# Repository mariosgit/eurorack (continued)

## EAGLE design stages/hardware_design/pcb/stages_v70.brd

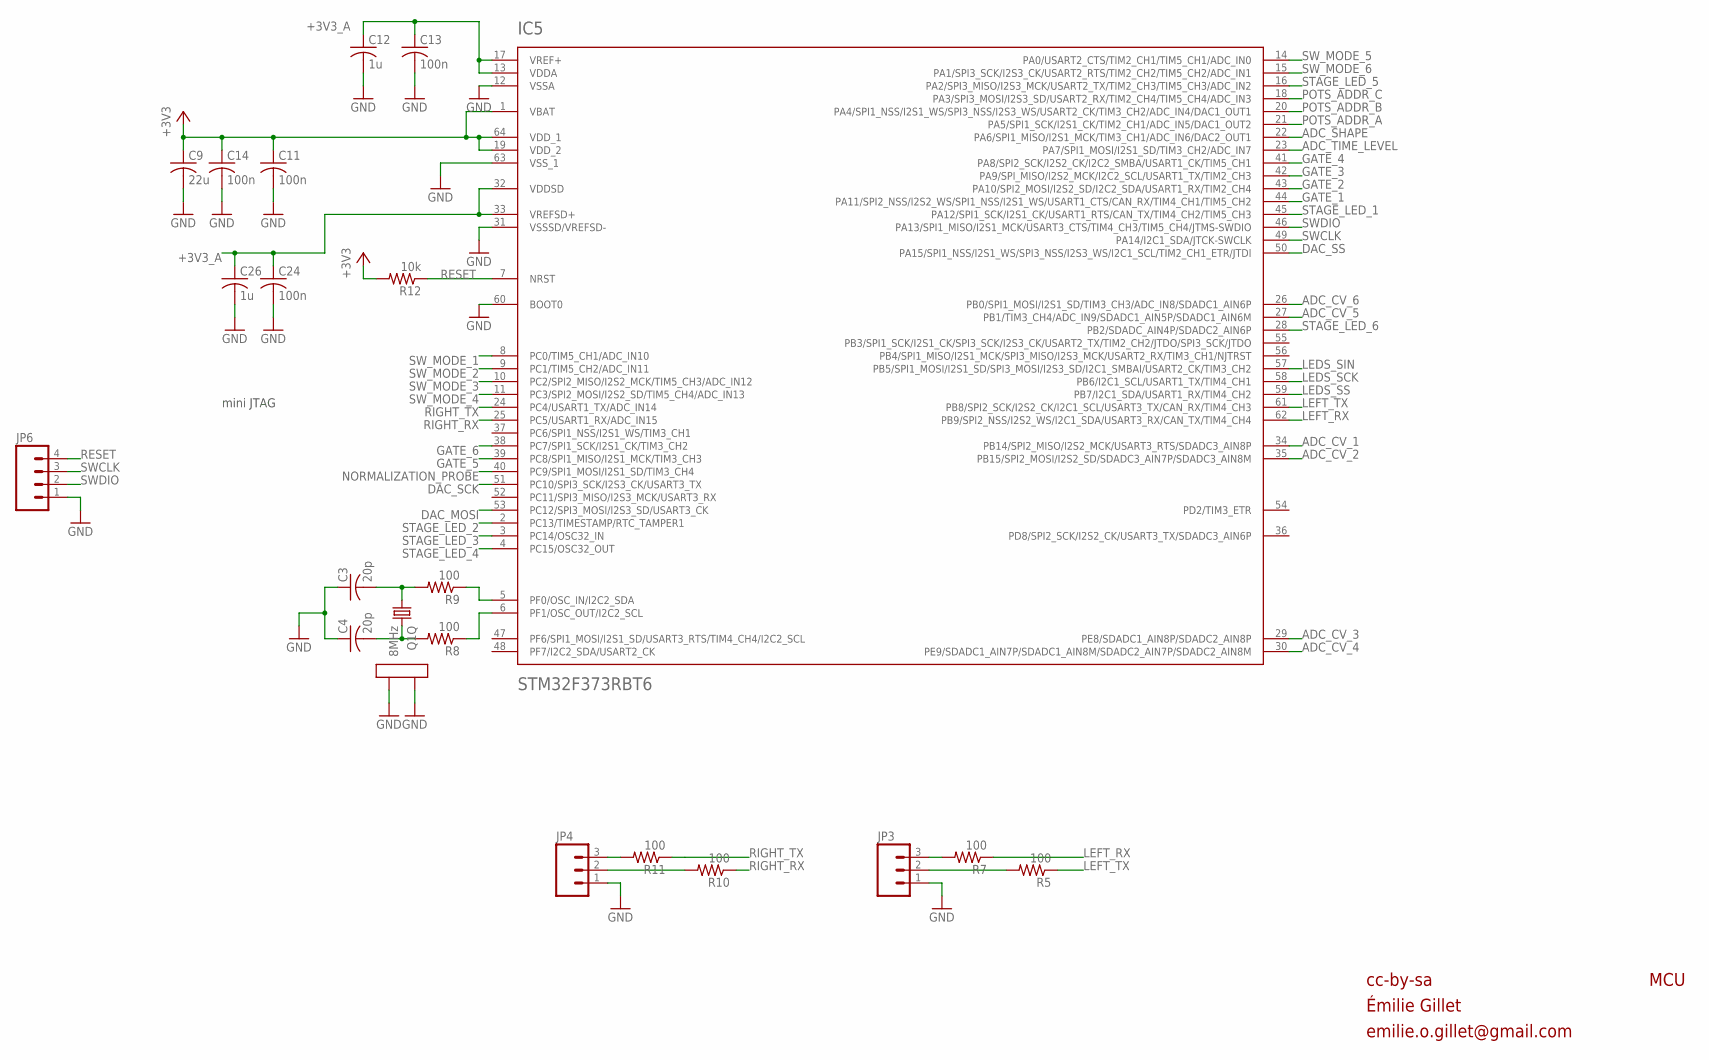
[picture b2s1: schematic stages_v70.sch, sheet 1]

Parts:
C3, C4: 20p; C0402
C9: 22u; C1206
C11, C13, C14, C24: 100n; C0402
C12, C26: 1u; C0402
IC5: STM32F373RBT6; TQFP-10X10-64
JP3, JP4: M03PTH; 1X03
JP6: M04PTH; 1X04
Q1: 8MHz; CTS406
R5, R7, R8, R9, R10, R11: 100; R0402
R12: 10k; R0402

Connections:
+3V3: C9.1, C11.1, C14.1, IC5.1 (VBAT), IC5.19 (VDD_2), IC5.64 (VDD_1), R12.2; also elsewhere on the board
+3V3_A: C12.1, C13.1, C24.1, C26.1, IC5.13 (VDDA), IC5.17 (VREF+), IC5.32 (VDDSD), IC5.33 (VREFSD+); also elsewhere on the board
ADC_CV_1: IC5.34 (PB14/SPI2_MISO/I2S2_MCK/USART3_RTS/SDAD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); also elsewhere on the board
ADC_CV_2: IC5.35 (PB15/SPI2_MOSI/I2S2_SD/SDADC3_AIN7P/SDA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); also elsewhere on the board
ADC_CV_3: IC5.29 (PE8/SDADC1_AIN8P/SDADC2_AIN8P); also elsewhere on the board
ADC_CV_4: IC5.30 (PE9/SDADC1_AIN7P/SDADC1_AIN8M/SDADC2_AI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); also elsewhere on the board
ADC_CV_5: IC5.27 (PB1/TIM3_CH4/ADC_IN9/SDADC1_AIN5P/SDADC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); also elsewhere on the board
ADC_CV_6: IC5.26 (PB0/SPI1_MOSI/I2S1_SD/TIM3_CH3/ADC_IN8/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); also elsewhere on the board
ADC_SHAPE: IC5.22 (PA6/SPI1_MISO/I2S1_MCK/TIM3_CH1/ADC_IN6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); also elsewhere on the board
ADC_TIME_LEVEL: IC5.23 (PA7/SPI1_MOSI/I2S1_SD/TIM3_CH2/ADC_IN7); also elsewhere on the board
DAC_MOSI: IC5.53 (PC12/SPI3_MOSI/I2S3_SD/USART3_CK); also elsewhere on the board
DAC_SCK: IC5.51 (PC10/SPI3_SCK/I2S3_CK/USART3_TX); also elsewhere on the board
DAC_SS: IC5.50 (PA15/SPI1_NSS/I2S1_WS/SPI3_NSS/I2S3_WS/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); also elsewhere on the board
GATE_1: IC5.44 (PA11/SPI2_NSS/I2S2_WS/SPI1_NSS/I2S1_WS/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); also elsewhere on the board
GATE_2: IC5.43 (PA10/SPI2_MOSI/I2S2_SD/I2C2_SDA/USART1_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); also elsewhere on the board
GATE_3: IC5.42 (PA9/SPI_MISO/I2S2_MCK/I2C2_SCL/USART1_T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); also elsewhere on the board
GATE_4: IC5.41 (PA8/SPI2_SCK/I2S2_CK/I2C2_SMBA/USART1_C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); also elsewhere on the board
GATE_5: IC5.39 (PC8/SPI1_MISO/I2S1_MCK/TIM3_CH3); also elsewhere on the board
GATE_6: IC5.38 (PC7/SPI1_SCK/I2S1_CK/TIM3_CH2); also elsewhere on the board
GND: C3.1, C4.1, C9.2, C11.2, C12.2, C13.2, C14.2, C24.2, C26.2, IC5.12 (VSSA), IC5.31 (VSSSD/VREFSD-), IC5.60 (BOOT0), IC5.63 (VSS_1), JP3.1, JP4.1, JP6.1, Q1.2 (LID1), Q1.4 (LID2); also elsewhere on the board
LEDS_SCK: IC5.58 (PB6/I2C1_SCL/USART1_TX/TIM4_CH1); also elsewhere on the board
LEDS_SIN: IC5.57 (PB5/SPI1_MOSI/I2S1_SD/SPI3_MOSI/I2S3_SD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); also elsewhere on the board
LEDS_SS: IC5.59 (PB7/I2C1_SDA/USART1_RX/TIM4_CH2); also elsewhere on the board
LEFT_RX: IC5.62 (PB9/SPI2_NSS/I2S2_WS/I2C1_SDA/USART3_RX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), R7.1
LEFT_RX_R: JP3.3, R7.2
LEFT_TX: IC5.61 (PB8/SPI2_SCK/I2S2_CK/I2C1_SCL/USART3_TX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), R5.1
LEFT_TX_R: JP3.2, R5.2
unnamed: C3.2, Q1.1, R9.2
unnamed: C4.2, Q1.3 (2), R8.2
unnamed: IC5.5 (PF0/OSC_IN/I2C2_SDA), R9.1
unnamed: IC5.6 (PF1/OSC_OUT/I2C2_SCL), R8.1
NORMALIZATION_PROBE: IC5.40 (PC9/SPI1_MOSI/I2S1_SD/TIM3_CH4); also elsewhere on the board
POTS_ADDR_A: IC5.21 (PA5/SPI1_SCK/I2S1_CK/TIM2_CH1/ADC_IN5/D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); also elsewhere on the board
POTS_ADDR_B: IC5.20 (PA4/SPI1_NSS/I2S1_WS/SPI3_NSS/I2S3_WS/U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); also elsewhere on the board
POTS_ADDR_C: IC5.18 (PA3/SPI3_MOSI/I2S3_SD/USART2_RX/TIM2_CH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); also elsewhere on the board
RESET: IC5.7 (NRST), JP6.4, R12.1
RIGHT_RX: IC5.25 (PC5/USART1_RX/ADC_IN15), R10.1
RIGHT_RX_R: JP4.2, R10.2
RIGHT_TX: IC5.24 (PC4/USART1_TX/ADC_IN14), R11.1
RIGHT_TX_R: JP4.3, R11.2
STAGE_LED_1: IC5.45 (PA12/SPI1_SCK/I2S1_CK/USART1_RTS/CAN_TX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); also elsewhere on the board
STAGE_LED_2: IC5.2 (PC13/TIMESTAMP/RTC_TAMPER1); also elsewhere on the board
STAGE_LED_3: IC5.3 (PC14/OSC32_IN); also elsewhere on the board
STAGE_LED_4: IC5.4 (PC15/OSC32_OUT); also elsewhere on the board
STAGE_LED_5: IC5.16 (PA2/SPI3_MISO/I2S3_MCK/USART2_TX/TIM2_C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); also elsewhere on the board
STAGE_LED_6: IC5.28 (PB2/SDADC_AIN4P/SDADC2_AIN6P); also elsewhere on the board
SWCLK: IC5.49 (PA14/I2C1_SDA/JTCK-SWCLK), JP6.3
SWDIO: IC5.46 (PA13/SPI1_MISO/I2S1_MCK/USART3_CTS/TIM4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), JP6.2
SW_MODE_1: IC5.8 (PC0/TIM5_CH1/ADC_IN10); also elsewhere on the board
SW_MODE_2: IC5.9 (PC1/TIM5_CH2/ADC_IN11); also elsewhere on the board
SW_MODE_3: IC5.10 (PC2/SPI2_MISO/I2S2_MCK/TIM5_CH3/ADC_IN12); also elsewhere on the board
SW_MODE_4: IC5.11 (PC3/SPI2_MOSI/I2S2_SD/TIM5_CH4/ADC_IN13); also elsewhere on the board
SW_MODE_5: IC5.14 (PA0/USART2_CTS/TIM2_CH1/TIM5_CH1/ADC_IN0); also elsewhere on the board
SW_MODE_6: IC5.15 (PA1/SPI3_SCK/I2S3_CK/USART2_RTS/TIM2_CH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); also elsewhere on the board

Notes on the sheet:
cc-by-sa
MCU
mini JTAG
Émilie Gillet
emilie.o.gillet@gmail.com

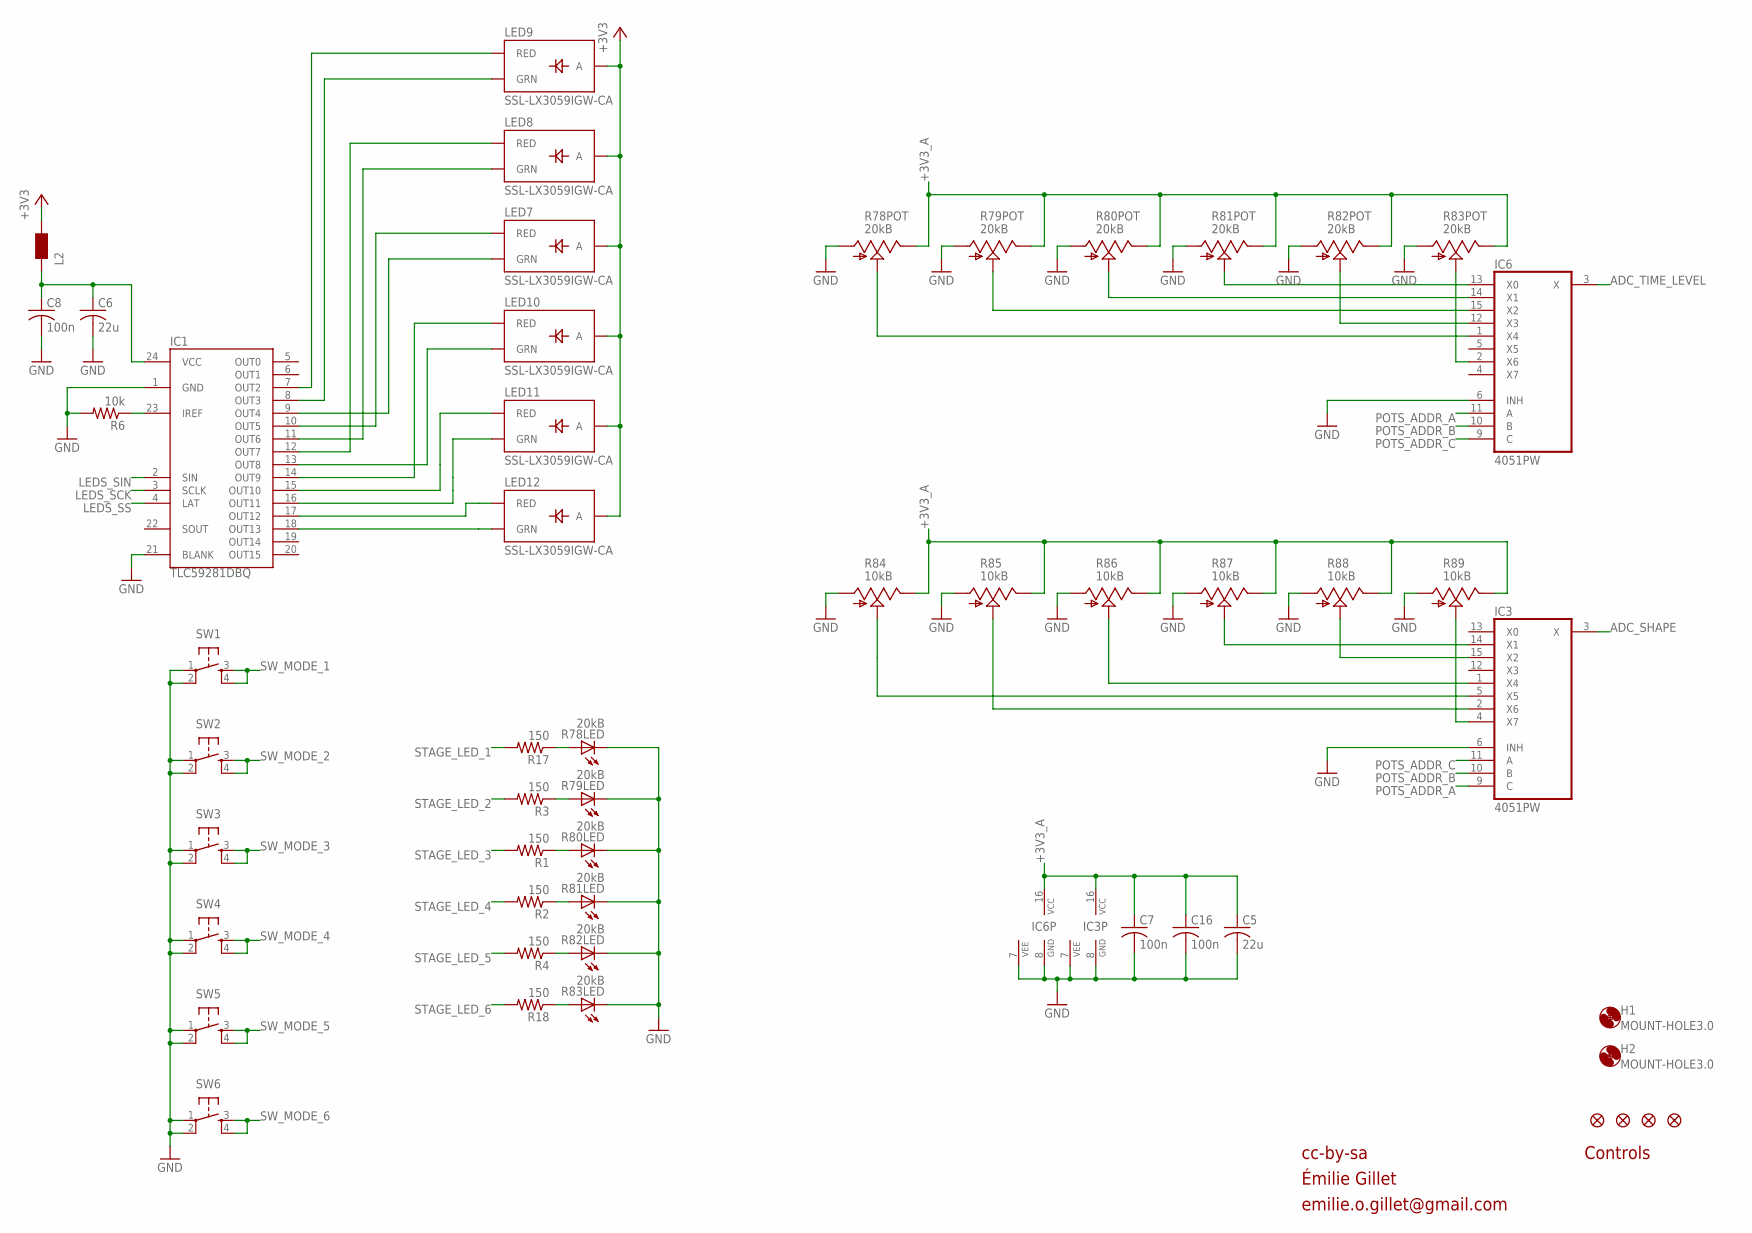
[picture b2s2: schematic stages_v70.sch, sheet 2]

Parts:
C5, C6: 22u; C1206
C7, C8, C16: 100n; C0402
H1, H2: MOUNT-HOLE3.0; 3,0
IC1: TLC59281DBQ; TSSOP24_0635
IC3, IC6: 4051PW; TSSOP16_065
JP1, JP2, JP7, JP8: FIDUCIAL1X2; FIDUCIAL-1X2
L2: WE-CBF_0603; 0603
LED7, LED8, LED9, LED10, LED11, LED12: SSL-LX3059IGW-CA; LED-BICOLOR-THROUGHHOLE-LUMEX
R1, R2, R3, R4, R17, R18: 150; R0402
R6: 10k; R0402
R78, R79, R80, R81, R82, R83: 20kB; BOURNS_SLIDER
R84, R85, R86, R87, R88, R89: 10kB; ALPS_POT_NARROW
SW1, SW2, SW3, SW4, SW5, SW6: TAC_SWITCHPTH; TACTILE-PTH

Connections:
+3V3: L2.2, LED7.A, LED8.A, LED9.A, LED10.A, LED11.A, LED12.A; also elsewhere on the board
+3V3_A: C5.1, C7.1, C16.1, IC3.16 (VCC), IC6.16 (VCC), R78.3 (E), R79.3 (E), R80.3 (E), R81.3 (E), R82.3 (E), R83.3 (E), R84.P$1 (E), R85.P$1 (E), R86.P$1 (E), R87.P$1 (E), R88.P$1 (E), R89.P$1 (E); also elsewhere on the board
ADC_SHAPE: IC3.3 (X); also elsewhere on the board
ADC_TIME_LEVEL: IC6.3 (X); also elsewhere on the board
GND: C5.2, C6.2, C7.2, C8.2, C16.2, IC1.1 (GND), IC1.21 (BLANK), IC3.6 (INH), IC3.7 (VEE), IC3.8 (GND), IC6.6 (INH), IC6.7 (VEE), IC6.8 (GND), R6.2, R78.1 (A), R78.E (C), R79.1 (A), R79.E (C), R80.1 (A), R80.E (C), R81.1 (A), R81.E (C), R82.1 (A), R82.E (C), R83.1 (A), R83.E (C), R84.P$3 (A), R85.P$3 (A), R86.P$3 (A), R87.P$3 (A), R88.P$3 (A), R89.P$3 (A), SW1.1, SW1.2, SW2.1, SW2.2, SW3.1, SW3.2, SW4.1, SW4.2, SW5.1, SW5.2, SW6.1, SW6.2; also elsewhere on the board
LEDS_SCK: IC1.3 (SCLK); also elsewhere on the board
LEDS_SIN: IC1.2 (SIN); also elsewhere on the board
LEDS_SS: IC1.4 (LAT); also elsewhere on the board
unnamed: IC1.10 (OUT5), LED7.RED_C (RED)
unnamed: IC1.18 (OUT13), LED12.GREEN_C (GRN)
unnamed: IC1.12 (OUT7), LED8.RED_C (RED)
unnamed: IC1.7 (OUT2), LED9.RED_C (RED)
unnamed: IC1.8 (OUT3), LED9.GREEN_C (GRN)
unnamed: IC1.13 (OUT8), LED10.GREEN_C (GRN)
unnamed: IC1.15 (OUT10), LED11.RED_C (RED)
unnamed: R17.1, R78.B (A)
unnamed: IC1.16 (OUT11), LED11.GREEN_C (GRN)
unnamed: IC1.17 (OUT12), LED12.RED_C (RED)
unnamed: IC1.11 (OUT6), LED8.GREEN_C (GRN)
unnamed: C6.1, C8.1, IC1.24 (VCC), L2.1
unnamed: IC1.14 (OUT9), LED10.RED_C (RED)
unnamed: IC6.1 (X4), R78.2 (S)
unnamed: R18.1, R83.B (A)
unnamed: IC6.2 (X6), R83.2 (S)
unnamed: IC6.12 (X3), R82.2 (S)
unnamed: IC6.13 (X0), R81.2 (S)
unnamed: IC6.14 (X1), R80.2 (S)
unnamed: IC6.15 (X2), R79.2 (S)
unnamed: IC3.2 (X6), R85.P$2 (S)
unnamed: IC3.4 (X7), R89.P$2 (S)
unnamed: IC3.1 (X4), R86.P$2 (S)
unnamed: IC3.14 (X1), R87.P$2 (S)
unnamed: IC3.15 (X2), R88.P$2 (S)
unnamed: IC3.5 (X5), R84.P$2 (S)
unnamed: R4.1, R82.B (A)
unnamed: IC1.23 (IREF), R6.1
unnamed: R2.1, R81.B (A)
unnamed: IC1.9 (OUT4), LED7.GREEN_C (GRN)
unnamed: R1.1, R80.B (A)
unnamed: R3.1, R79.B (A)
POTS_ADDR_A: IC3.9 (C), IC6.11 (A); also elsewhere on the board
POTS_ADDR_B: IC3.10 (B), IC6.10 (B); also elsewhere on the board
POTS_ADDR_C: IC3.11 (A), IC6.9 (C); also elsewhere on the board
STAGE_LED_1: R17.2; also elsewhere on the board
STAGE_LED_2: R3.2; also elsewhere on the board
STAGE_LED_3: R1.2; also elsewhere on the board
STAGE_LED_4: R2.2; also elsewhere on the board
STAGE_LED_5: R4.2; also elsewhere on the board
STAGE_LED_6: R18.2; also elsewhere on the board
SW_MODE_1: SW1.3, SW1.4; also elsewhere on the board
SW_MODE_2: SW2.3, SW2.4; also elsewhere on the board
SW_MODE_3: SW3.3, SW3.4; also elsewhere on the board
SW_MODE_4: SW4.3, SW4.4; also elsewhere on the board
SW_MODE_5: SW5.3, SW5.4; also elsewhere on the board
SW_MODE_6: SW6.3, SW6.4; also elsewhere on the board

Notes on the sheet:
cc-by-sa
Controls
Émilie Gillet
emilie.o.gillet@gmail.com

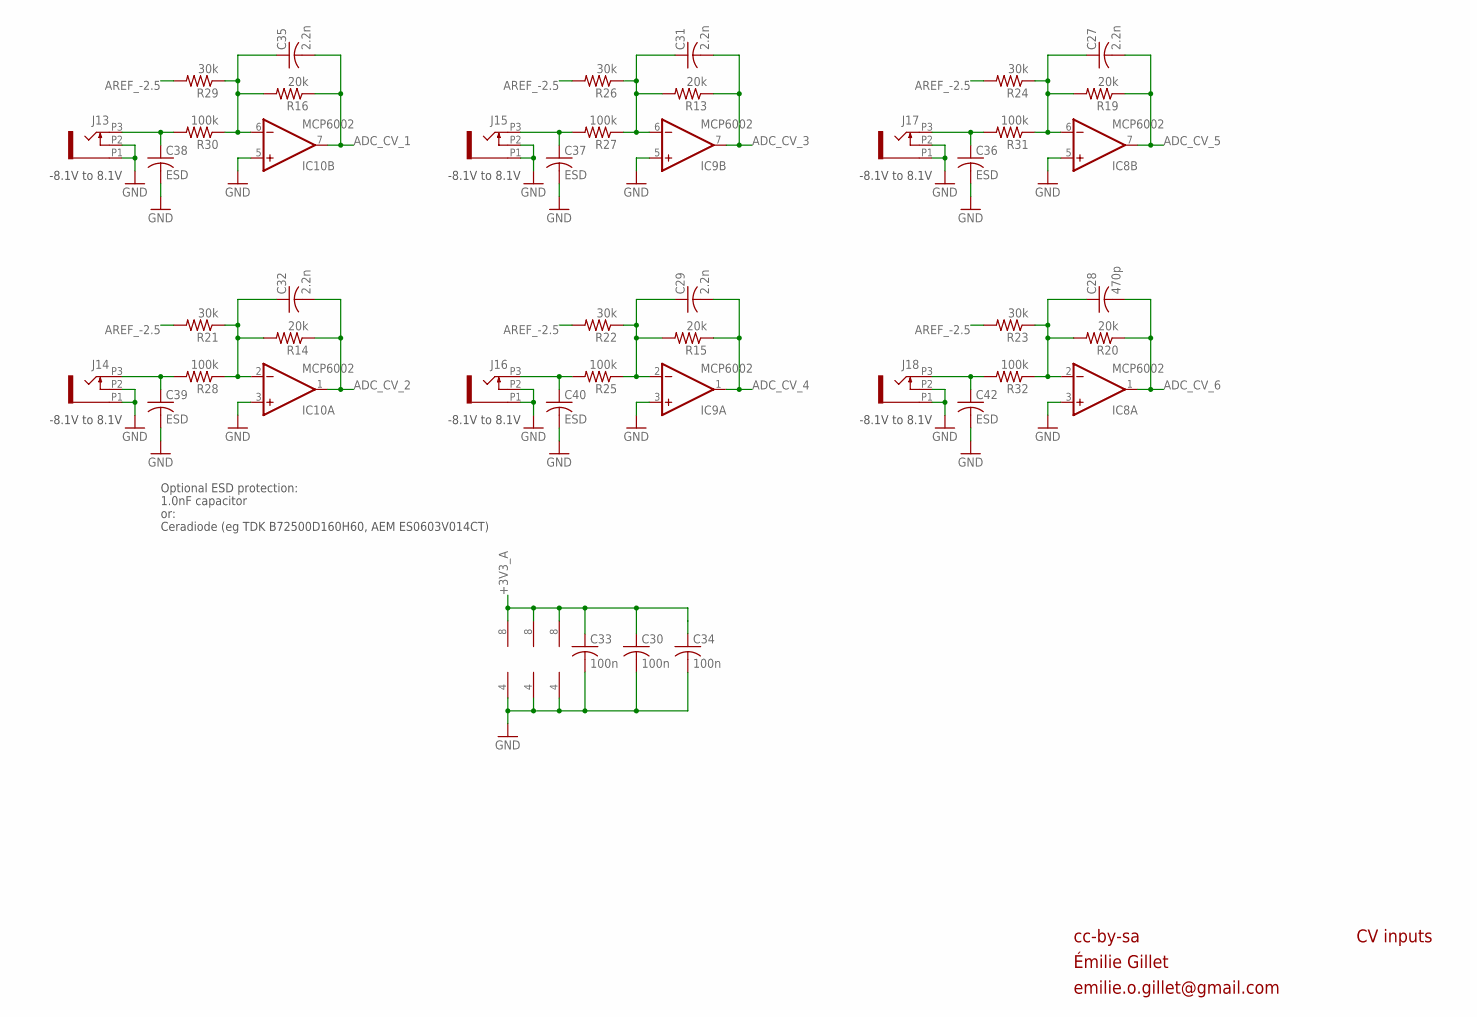
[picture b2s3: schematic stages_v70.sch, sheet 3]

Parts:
C27, C29, C31, C32, C35: 2.2n; C0402
C28: 470p; C0402
C30, C33, C34: 100n; C0402
C36, C37, C38, C39, C40, C42: ESD; C0603
IC8, IC9, IC10: MCP6002; MSOP-8
J13, J14, J15, J16, J17, J18: PJ301_THONKICONN6; WQP_PJ_301M6
R13, R14, R15, R16, R19, R20: 20k; R0402
R21, R22, R23, R24, R26, R29: 30k; R0402
R25, R27, R28, R30, R31, R32: 100k; R0402

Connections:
+3V3_A: C30.1, C33.1, C34.1, IC8.8 (V+), IC9.8 (V+), IC10.8 (V+); also elsewhere on the board
ADC_CV_1: C35.2, IC10.7 (OUT), R16.1; also elsewhere on the board
ADC_CV_2: C32.2, IC10.1 (OUT), R14.1; also elsewhere on the board
ADC_CV_3: C31.2, IC9.7 (OUT), R13.1; also elsewhere on the board
ADC_CV_4: C29.2, IC9.1 (OUT), R15.1; also elsewhere on the board
ADC_CV_5: C27.2, IC8.7 (OUT), R19.1; also elsewhere on the board
ADC_CV_6: C28.2, IC8.1 (OUT), R20.1; also elsewhere on the board
AREF_-2.5: R21.2, R22.2, R23.2, R24.2, R26.2, R29.2; also elsewhere on the board
GND: C30.2, C33.2, C34.2, C36.2, C37.2, C38.2, C39.2, C40.2, C42.2, IC8.3 (+IN), IC8.4 (V-), IC8.5 (+IN), IC9.3 (+IN), IC9.4 (V-), IC9.5 (+IN), IC10.3 (+IN), IC10.4 (V-), IC10.5 (+IN), J13.P1 (1), J13.P2 (2), J14.P1 (1), J14.P2 (2), J15.P1 (1), J15.P2 (2), J16.P1 (1), J16.P2 (2), J17.P1 (1), J17.P2 (2), J18.P1 (1), J18.P2 (2); also elsewhere on the board
MORPH_IN: C38.1, J13.P3 (3), R30.2
MORPH_IN1: C39.1, J14.P3 (3), R28.2
MORPH_IN2: C37.1, J15.P3 (3), R27.2
MORPH_IN3: C40.1, J16.P3 (3), R25.2
MORPH_IN4: C36.1, J17.P3 (3), R31.2
MORPH_IN5: C42.1, J18.P3 (3), R32.2
unnamed: C35.1, IC10.6 (-IN), R16.2, R29.1, R30.1
unnamed: C32.1, IC10.2 (-IN), R14.2, R21.1, R28.1
unnamed: C31.1, IC9.6 (-IN), R13.2, R26.1, R27.1
unnamed: C29.1, IC9.2 (-IN), R15.2, R22.1, R25.1
unnamed: C27.1, IC8.6 (-IN), R19.2, R24.1, R31.1
unnamed: C28.1, IC8.2 (-IN), R20.2, R23.1, R32.1

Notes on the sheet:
cc-by-sa
CV inputs
-8.1V to 8.1V
Optional ESD protection:
1.0nF capacitor
or:
Ceradiode (eg TDK B72500D160H60, AEM ES0603V014CT)
Émilie Gillet
emilie.o.gillet@gmail.com

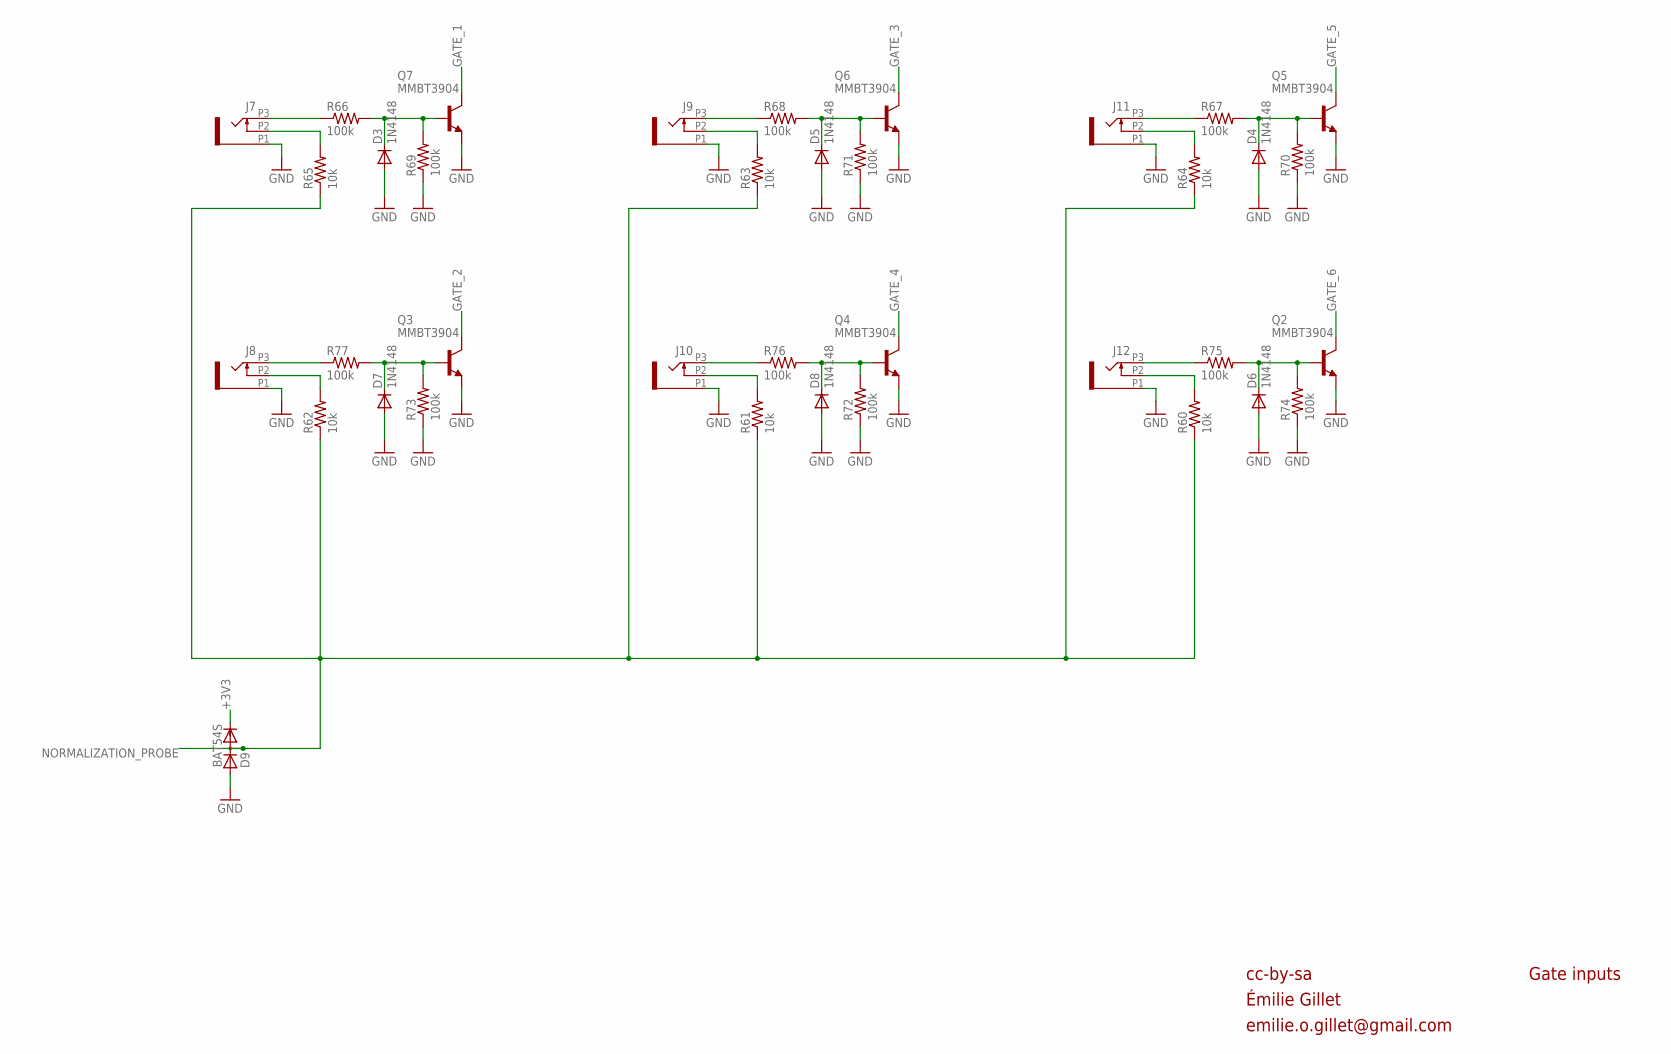
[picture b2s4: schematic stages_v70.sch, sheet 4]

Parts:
D3, D4, D5, D6, D7, D8: 1N4148; SOD523
D9: BAT54S; SOT23
J7, J8, J9, J10, J11, J12: PJ301_THONKICONN6; WQP_PJ_301M6
Q2, Q3, Q4, Q5, Q6, Q7: MMBT3904; SOT23-BEC
R60, R61, R62, R63, R64, R65: 10k; R0402
R66, R67, R68, R69, R70, R71, R72, R73, R74, R75, R76, R77: 100k; R0402

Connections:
+3V3: D9.2 (C); also elsewhere on the board
GATE_1: Q7.C; also elsewhere on the board
GATE_2: Q3.C; also elsewhere on the board
GATE_3: Q6.C; also elsewhere on the board
GATE_4: Q4.C; also elsewhere on the board
GATE_5: Q5.C; also elsewhere on the board
GATE_6: Q2.C; also elsewhere on the board
GND: D3.A, D4.A, D5.A, D6.A, D7.A, D8.A, D9.1 (A), J7.P1 (1), J8.P1 (1), J9.P1 (1), J10.P1 (1), J11.P1 (1), J12.P1 (1), Q2.E, Q3.E, Q4.E, Q5.E, Q6.E, Q7.E, R69.1, R70.1, R71.1, R72.1, R73.1, R74.1; also elsewhere on the board
unnamed: J9.P3 (3), R68.1
unnamed: J10.P3 (3), R76.1
unnamed: J10.P2 (2), R61.2
unnamed: J9.P2 (2), R63.2
unnamed: D5.C, Q6.B, R68.2, R71.2
unnamed: D8.C, Q4.B, R72.2, R76.2
unnamed: J11.P3 (3), R67.1
unnamed: J12.P3 (3), R75.1
unnamed: J12.P2 (2), R60.2
unnamed: J11.P2 (2), R64.2
unnamed: D4.C, Q5.B, R67.2, R70.2
unnamed: D6.C, Q2.B, R74.2, R75.2
unnamed: J8.P3 (3), R77.1
unnamed: J8.P2 (2), R62.2
unnamed: J7.P2 (2), R65.2
unnamed: D3.C, Q7.B, R66.2, R69.2
unnamed: D7.C, Q3.B, R73.2, R77.2
unnamed: J7.P3 (3), R66.1
NORMALIZATION_PROBE: D9.3 (AC), R60.1, R61.1, R62.1, R63.1, R64.1, R65.1; also elsewhere on the board

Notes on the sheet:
cc-by-sa
Gate inputs
Émilie Gillet
emilie.o.gillet@gmail.com

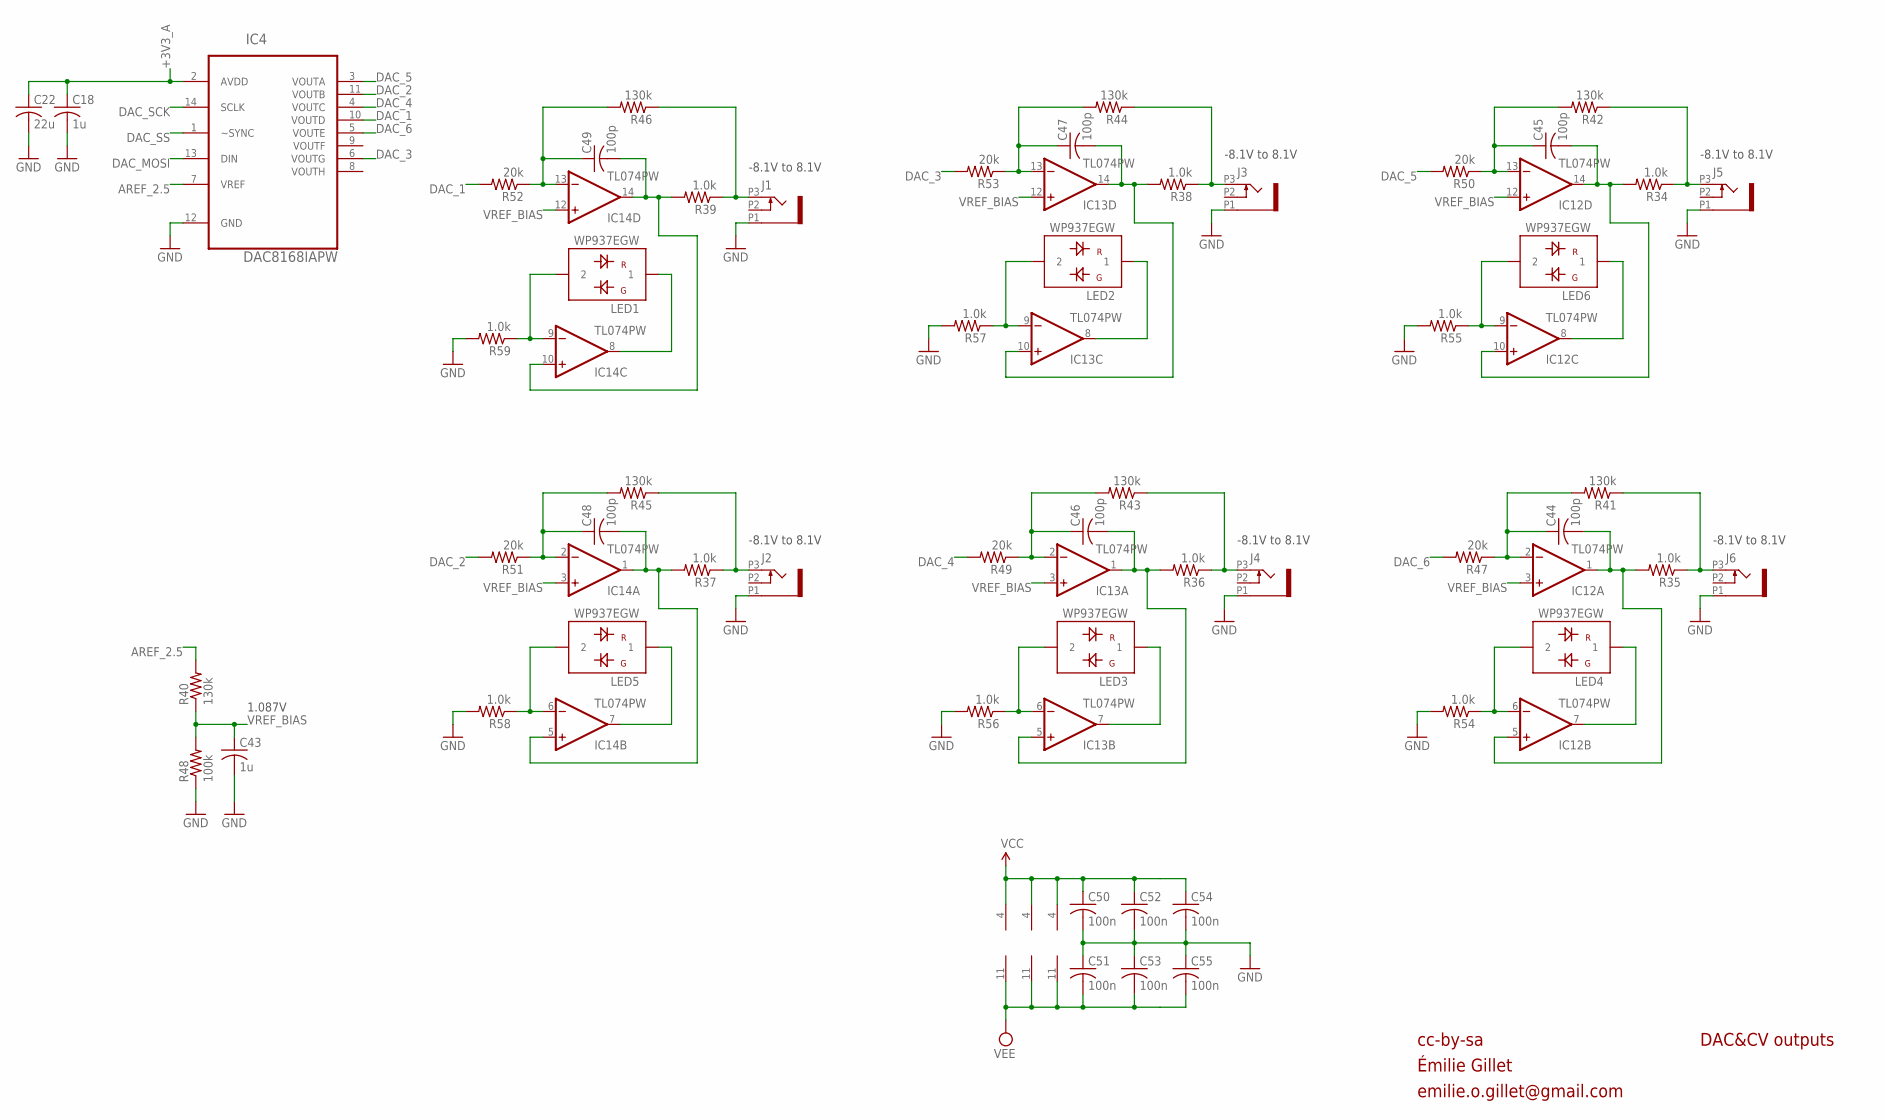
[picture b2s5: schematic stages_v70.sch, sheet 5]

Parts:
C18, C43: 1u; C0402
C22: 22u; C1206
C44, C45, C46, C47, C48, C49: 100p; C0402
C50, C51, C52, C53, C54, C55: 100n; C0402
IC4: DAC8168IAPW; RPDSOG14
IC12, IC13, IC14: TL074PW; TSSOP14_065
J1, J2, J3, J4, J5, J6: PJ301_THONKICONN6; WQP_PJ_301M6
LED1, LED2, LED3, LED4, LED5, LED6: WP937EGW; LED3MM
R34, R35, R36, R37, R38, R39: 1.0k; R0603
R40, R41, R42, R43, R44, R45, R46: 130k; R0402
R47, R49, R50, R51, R52, R53: 20k; R0402
R48: 100k; R0402
R54, R55, R56, R57, R58, R59: 1.0k; R0402

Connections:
+3V3_A: C18.1, C22.1, IC4.2 (AVDD); also elsewhere on the board
AREF_2.5: IC4.7 (VREF), R40.2
DAC_1: IC4.10 (VOUTD), R52.2
DAC_2: IC4.11 (VOUTB), R51.2
DAC_3: IC4.6 (VOUTG), R53.2
DAC_4: IC4.4 (VOUTC), R49.2
DAC_5: IC4.3 (VOUTA), R50.2
DAC_6: IC4.5 (VOUTE), R47.2
DAC_MOSI: IC4.13 (DIN); also elsewhere on the board
DAC_SCK: IC4.14 (SCLK); also elsewhere on the board
DAC_SS: IC4.1 (~SYNC); also elsewhere on the board
GND: C18.2, C22.2, C43.2, C50.2, C51.1, C52.2, C53.1, C54.2, C55.1, IC4.12 (GND), J1.P1 (1), J2.P1 (1), J3.P1 (1), J4.P1 (1), J5.P1 (1), J6.P1 (1), R48.1, R54.2, R55.2, R56.2, R57.2, R58.2, R59.2; also elsewhere on the board
unnamed: C49.2, IC14.10 (+IN), IC14.14 (OUT), R39.2
unnamed: J1.P3 (3), R39.1, R46.1
unnamed: J2.P3 (3), R37.1, R45.1
unnamed: J4.P3 (3), R36.1, R43.1
unnamed: C46.1, IC13.2 (-IN), R43.2, R49.1
unnamed: C48.1, IC14.2 (-IN), R45.2, R51.1
unnamed: C47.1, IC13.13 (-IN), R44.2, R53.1
unnamed: C49.1, IC14.13 (-IN), R46.2, R52.1
unnamed: J3.P3 (3), R38.1, R44.1
unnamed: IC14.9 (-IN), LED1.2, R59.1
unnamed: IC14.8 (OUT), LED1.1
unnamed: C47.2, IC13.10 (+IN), IC13.14 (OUT), R38.2
unnamed: IC13.9 (-IN), LED2.2, R57.1
unnamed: IC13.8 (OUT), LED2.1
unnamed: C48.2, IC14.1 (OUT), IC14.5 (+IN), R37.2
unnamed: IC14.6 (-IN), LED5.2, R58.1
unnamed: IC14.7 (OUT), LED5.1
unnamed: C46.2, IC13.1 (OUT), IC13.5 (+IN), R36.2
unnamed: IC13.6 (-IN), LED3.2, R56.1
unnamed: IC13.7 (OUT), LED3.1
unnamed: J6.P3 (3), R35.1, R41.1
unnamed: C44.1, IC12.2 (-IN), R41.2, R47.1
unnamed: C45.1, IC12.13 (-IN), R42.2, R50.1
unnamed: J5.P3 (3), R34.1, R42.1
unnamed: C45.2, IC12.10 (+IN), IC12.14 (OUT), R34.2
unnamed: IC12.9 (-IN), LED6.2, R55.1
unnamed: IC12.8 (OUT), LED6.1
unnamed: C44.2, IC12.1 (OUT), IC12.5 (+IN), R35.2
unnamed: IC12.6 (-IN), LED4.2, R54.1
unnamed: IC12.7 (OUT), LED4.1
VCC: C50.1, C52.1, C54.1, IC12.4 (V+), IC13.4 (V+), IC14.4 (V+); also elsewhere on the board
VEE: C51.2, C53.2, C55.2, IC12.11 (V-), IC13.11 (V-), IC14.11 (V-); also elsewhere on the board
VREF_BIAS: C43.1, IC12.3 (+IN), IC12.12 (+IN), IC13.3 (+IN), IC13.12 (+IN), IC14.3 (+IN), IC14.12 (+IN), R40.1, R48.2

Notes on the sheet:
cc-by-sa
DAC&CV outputs
-8.1V to 8.1V
1.087V
Émilie Gillet
emilie.o.gillet@gmail.com

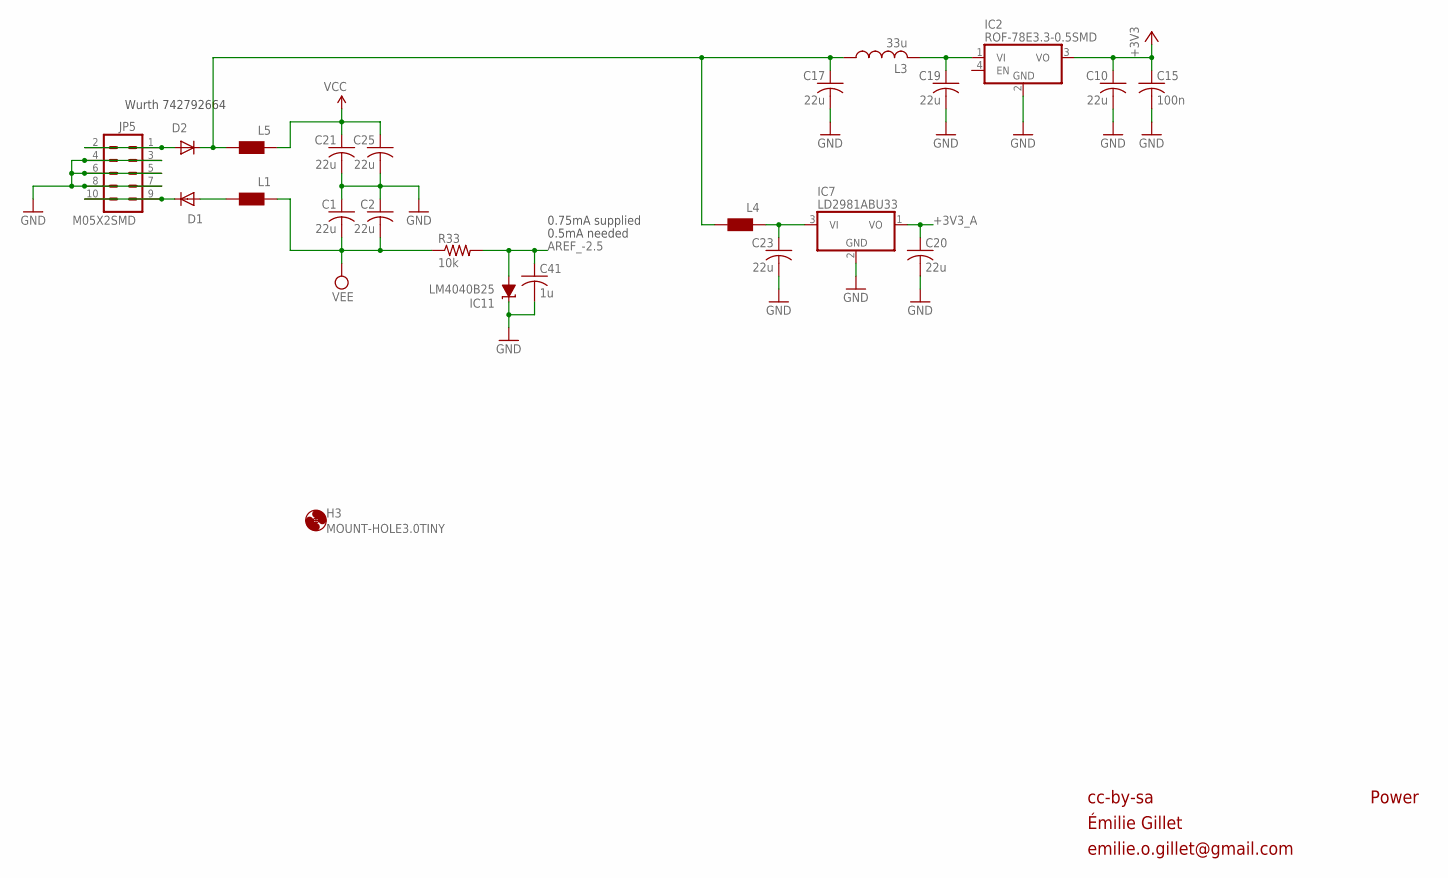
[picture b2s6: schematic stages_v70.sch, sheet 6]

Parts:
C1, C2, C10, C17, C19, C20, C21, C23, C25: 22u; C1206
C15: 100n; C0402
C41: 1u; C0402
D1, D2: 1N5819HW; SOD123
H3: MOUNT-HOLE3.0TINY; 3,0TINY
IC2: ROF-78E3.3-0.5SMD; ROF78EXX-0.5SMD
IC7: LD2981ABU33; SOT89
IC11: LM4040B25; DBZ_R-PDSO-G3
JP5: M05X2SMD; 2X5-SMD
L1, L4, L5: WE-CBF_0603; 0603
L3: 33u; L2012C
R33: 10k; R0402

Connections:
+3V3: C10.1, C15.1, IC2.3 (VO); also elsewhere on the board
+3V3_A: C20.1, IC7.1 (VO); also elsewhere on the board
AREF_-2.5: C41.1, IC11.2 (A), R33.2; also elsewhere on the board
GND: C1.1, C2.1, C10.2, C15.2, C17.2, C19.2, C20.2, C21.2, C23.2, C25.2, C41.2, IC2.2 (GND), IC7.2 (GND), IC11.1 (C), JP5.3, JP5.4, JP5.5, JP5.6, JP5.7, JP5.8; also elsewhere on the board
unnamed: D2.A, JP5.1, JP5.2
unnamed: D1.A, L1.2
unnamed: C23.1, IC7.3 (VI), L4.1
unnamed: C17.1, D2.C, L3.1, L4.2, L5.2
unnamed: D1.C, JP5.9, JP5.10
unnamed: C19.1, IC2.1 (VI), L3.2
VCC: C21.1, C25.1, L5.1; also elsewhere on the board
VEE: C1.2, C2.2, L1.1, R33.1; also elsewhere on the board

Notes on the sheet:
0.5mA needed
Wurth 742792664
0.75mA supplied
cc-by-sa
Power
Émilie Gillet
emilie.o.gillet@gmail.com

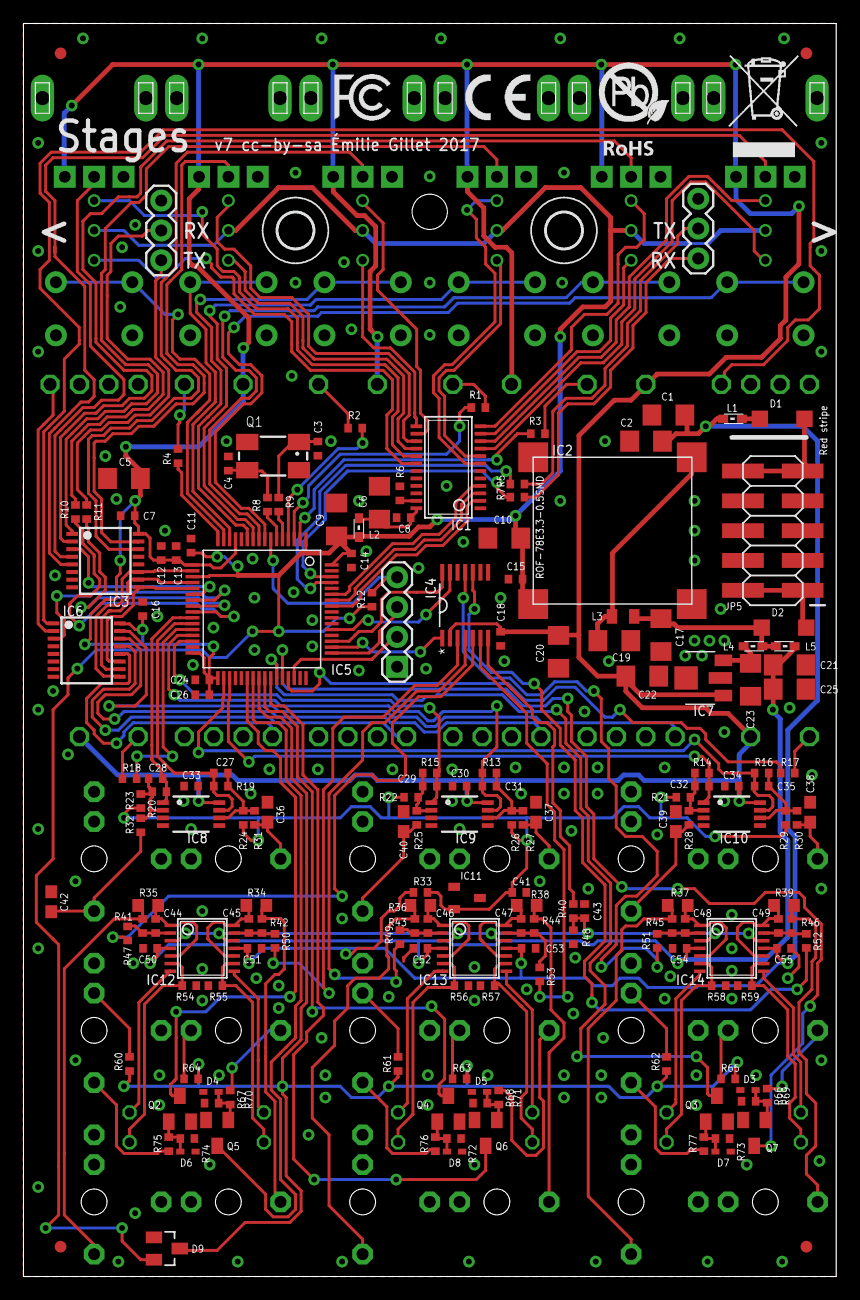
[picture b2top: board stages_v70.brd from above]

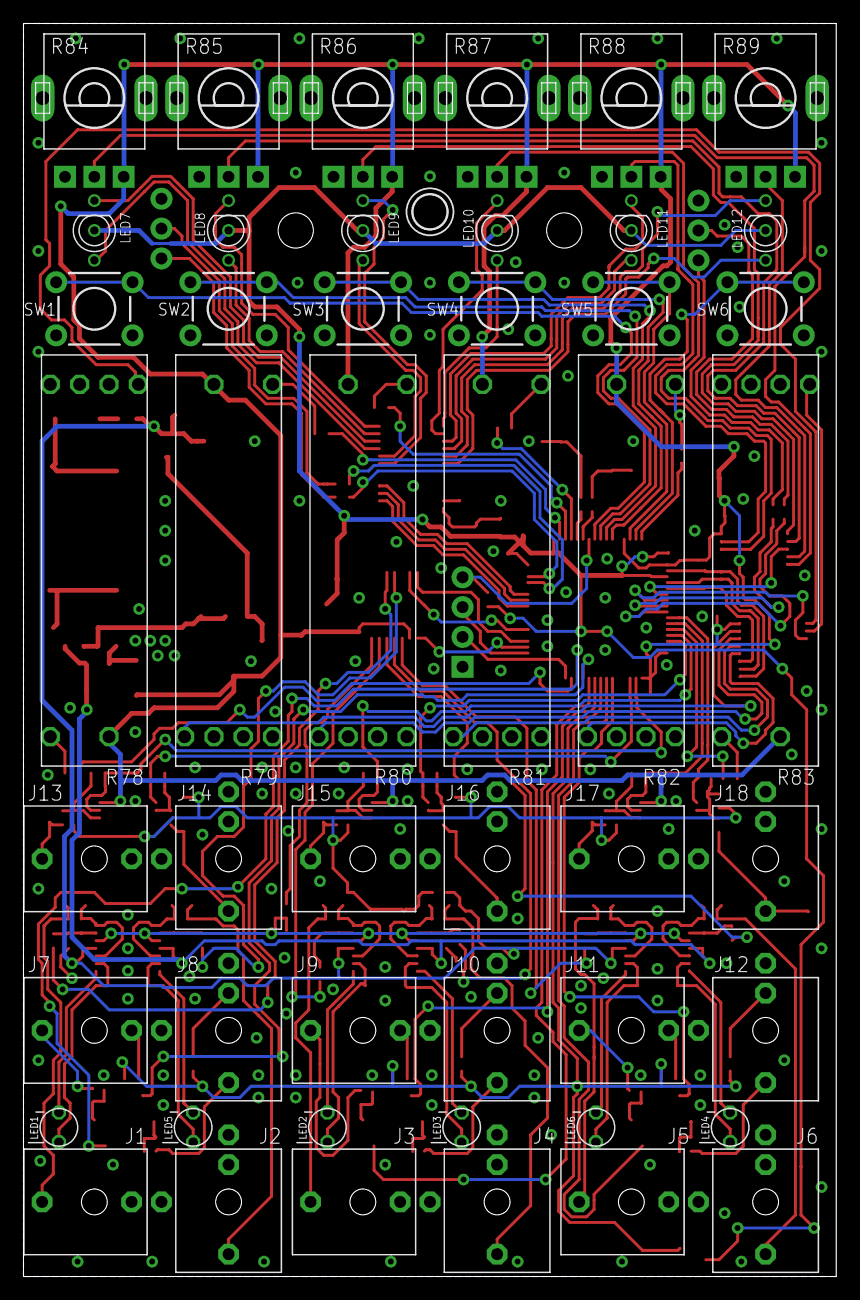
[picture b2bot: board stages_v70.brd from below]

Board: 2 copper layers, 69.2 x 106.7 mm, 230 parts (49 on the bottom side), 163 nets.

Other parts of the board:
U$1: ROHS
U$2: ROHS_2
U$3: FCC_SMALL
U$4: CE_SMALL

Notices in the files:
tides/hardware_design/pcb/tides_v40.brd:
cc-by-sa Émilie Gillet, 2015. v4
